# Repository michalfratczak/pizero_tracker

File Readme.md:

## I2C

You need to use software driver to I2C, and therefore, disable bluetooth. This is for rPI 3 and up.

[https://raspberrypi.stackexchange.com/questions/45570/how-do-i-make-serial-work-on-the-raspberry-pi3-or-later-model]

```
sudo rpi-update

nano /boot/config.txt

dtoverlay=pi3-disable-bt
enable_uart=1
dtoverlay=w1-gpio
dtparam=i2c_arm=off
dtparam=i2c=off
#dtoverlay=i2c-gpio,bus=1,i2c_gpio_sda=2,i2c_gpio_scl=3
dtoverlay=i2c-gpio,i2c_gpio_sda=2,i2c_gpio_scl=3
```

## Dependencies

SSDV:

git submodule update --init --recursive

---
sudo apt-get install libboost-program-options-dev

---
git clone https://github.com/zeromq/libzmq.git

build with cmake

---
git clone https://github.com/zeromq/cppzmq.git

build with cmake

---
http://abyz.me.uk/rpi/pigpio/download.html
```
wget https://github.com/joan2937/pigpio/archive/master.zip
unzip master.zip
cd pigpio-master
make
sudo make install
```

---
pip3 install zmq exifread picamera psutil

sudo apt-get install imagemagick

## Run on one thread:

```
taskset -c 1 ./tracker
```

## MTX2 datasheet
http://www.radiometrix.com/files/additional/mtx2.pdf

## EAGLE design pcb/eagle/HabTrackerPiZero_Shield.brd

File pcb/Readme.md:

IMPORTANT:
Powering to 3.3V from a regulator does not work here.
Instead, use 5V regulator and connect to 5V pin.

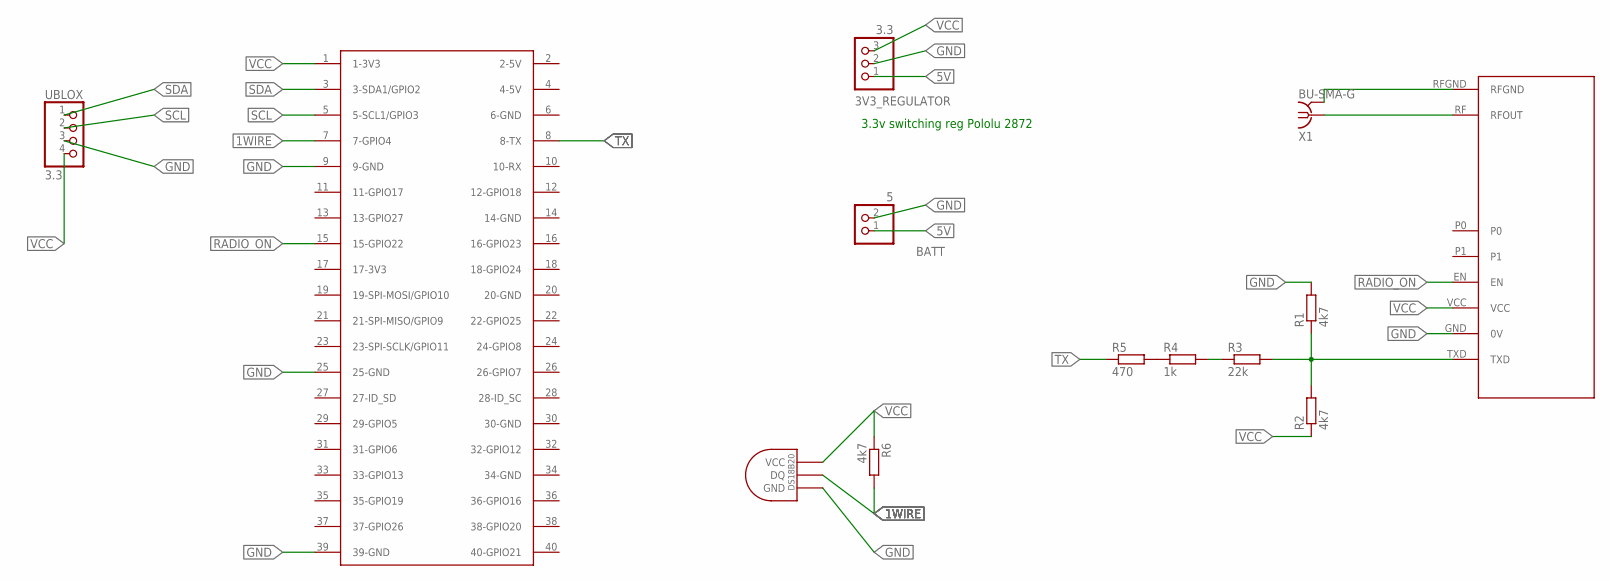
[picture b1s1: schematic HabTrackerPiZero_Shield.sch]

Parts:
3V3_REGULATOR: 3.3; 1X03
BATT: 5; 1X02
R1, R2, R6: 4k7; 0204/7
R3: 22k; 0204/7
R4: 1k; 0204/7
R5: 470; 0204/7
U$1: RASPBERRY-PI+PIZERO; RASPBERRY-PI-ZERO
U$2: DS1820TO92; DS1820
U$3: RADIOMETRIX-MTX2
UBLOX: 3.3; 1X04
X1: BU-SMA-G

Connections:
1WIRE: R6.2, U$1.7 (7-GPIO4), U$2.DQ
5V: 3V3_REGULATOR.1, BATT.1
GND: 3V3_REGULATOR.2, BATT.2, R1.2, U$1.9 (9-GND), U$1.25 (25-GND), U$1.39 (39-GND), U$2.GND, U$3.GND (0V), UBLOX.3
unnamed: R1.1, R2.2, R3.2, U$3.TXD
unnamed: U$3.RF (RFOUT), X1.1
unnamed: U$3.RFGND, X1.2, X1.3 (2), X1.4 (2), X1.5 (2)
unnamed: R4.1, R5.2
unnamed: R3.1, R4.2
RADIO_ON: U$1.15 (15-GPIO22), U$3.EN
SCL: U$1.5 (5-SCL1/GPIO3), UBLOX.2
SDA: U$1.3 (3-SDA1/GPIO2), UBLOX.1
TX: R5.1, U$1.8 (8-TX)
VCC: 3V3_REGULATOR.3, R2.1, R6.1, U$1.1 (1-3V3), U$2.VDD (VCC), U$3.VCC, UBLOX.4

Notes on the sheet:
3.3v switching reg Pololu 2872

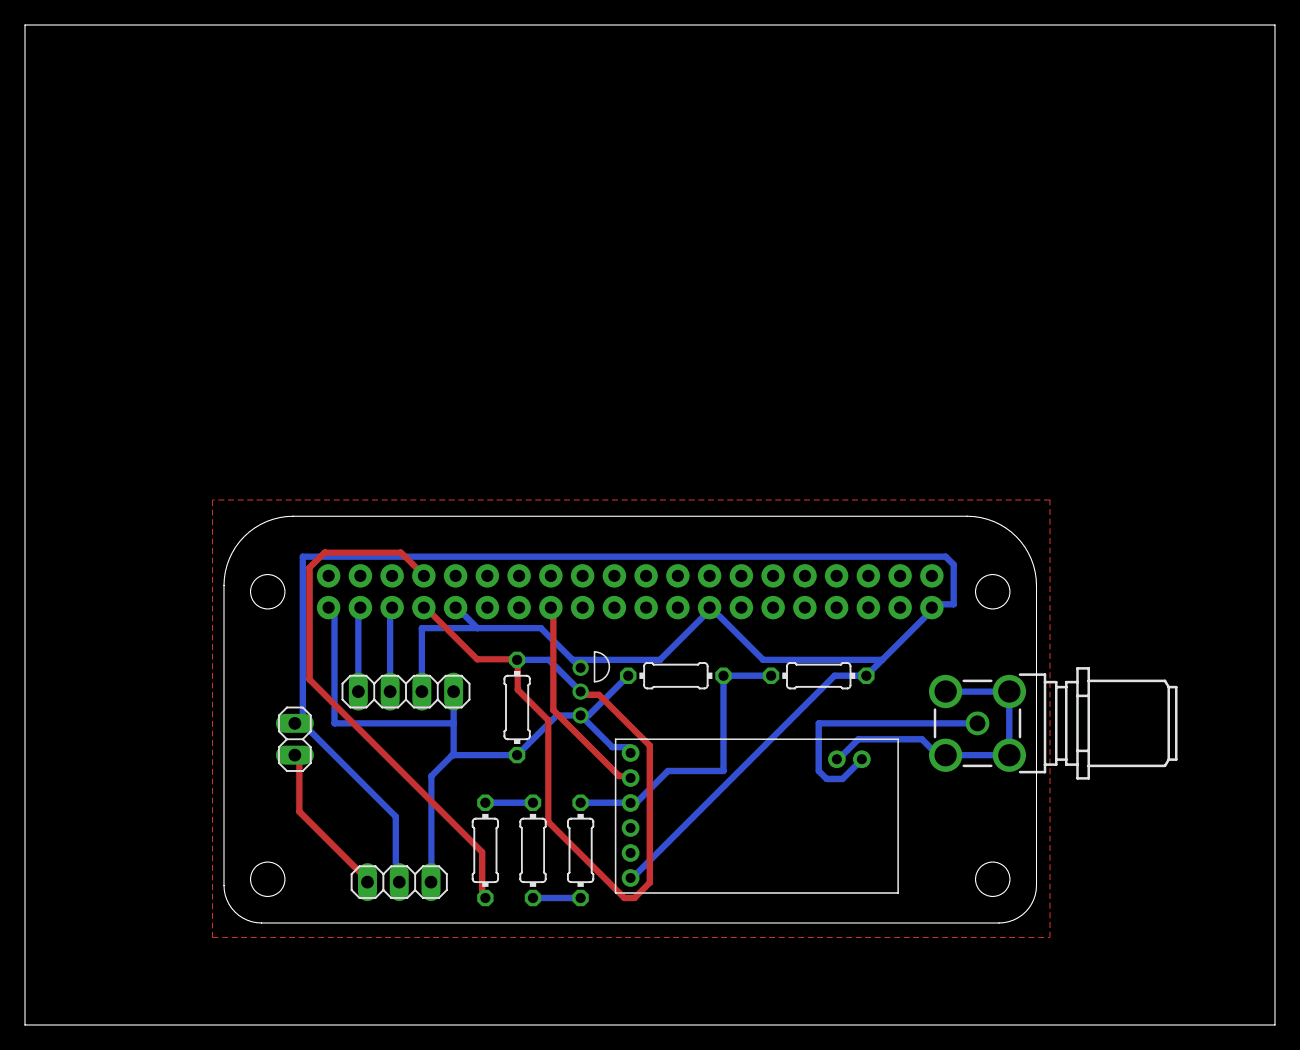
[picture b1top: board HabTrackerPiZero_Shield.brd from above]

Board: 2 copper layers, 100.0 x 80.0 mm, 13 parts (0 on the bottom side), 13 nets.

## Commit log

2020-03-29 add nmea and uBlox code
2020-03-29 uBlox move some code between files
2020-03-30 mtx2b init
2020-03-31 mtx2b - baud_t type
2020-03-31 eagle PCB files for board shield
2020-04-01 mtx2 wip
2020-04-01 squash mtx2 devel branch
2020-04-01 squash ds18b20 devel branch
2020-04-01 Readme.md
2020-04-01 dsb18b20 crc regexp fix
2020-04-01 minimal main tracker code
2020-04-02 tracker main.cpp minor cleanup
2020-04-02 improved NMEA scanning
2020-04-02 some nmea comments
2020-04-02 remove deg2decim from NMEA iface
2020-04-02 some formatting
2020-04-05 test message in UKHAS format
2020-04-08 Use NMEA_get_last_msg in ublox test
2020-04-08 main tracker: properly parse NMEA from uBlox
2020-04-08 nmea_t::utc is now char[6]
2020-04-08 fix nmea utc string formatting
2020-04-09 Add https://github.com/fsphil/ssdv
2020-04-09 ssdv CMake and test JPEG file
2020-04-09 example SSDV send
2020-04-09 remove k100 baud speed
2020-04-09 uBLOX as thread
2020-04-09 ssdv delete image after send
2020-04-10 Initial ZeroMQ. Private GLOB::nmea
2020-04-10 nmea_t comments. Add temp sensor to GLOB.
2020-04-11 msg_num CLI. baud_t : int.
2020-04-11 sensors thread
2020-04-11 static cppzmq linking
2020-04-11 add service file
2020-04-11 device acquire in loop. NMEA report UTC from incomplete sentences.
2020-04-11 Don't send SSDV when no fix. Added nmea_t::seconds()
2020-04-13 Fix CTRL_C in mainloop
2020-04-13 wip - cleanup
2020-04-13 dynamics
2020-04-14 nmea_t utc_as_seconds
2020-04-14 improved test zmq client
2020-04-15 Better GPS handling. Improved nmea parsing. Beter fix validation.
2020-04-15 Fixed clock in dynamics_t. All sensors in G.dynamics_
2020-04-15 basic camera.py
2020-04-15 camera.py zmq client
2020-04-15 JSON structure change.
2020-04-16 readme
2020-04-16 Fix bug in RMC parsing.
2020-04-16 Fixed dynamics_t
2020-04-16 dyncamics_t fixed dT
2020-04-16 dynamics_t: value always up-to-date
2020-04-16 code comments
2020-04-16 Fixed nmea reuse inmain loop
2020-04-16 dynamics_t improvements. with averaging.
2020-04-16 camera.py wip
2020-04-16 camera wip
2020-04-17 Camera WIP. camera.service. Always send SSDV.
2020-04-23 ssdv rename tile to packet
2020-05-12 setproctitle camera.py
2020-05-13 ssdv: delete file if failed to load data.
2020-05-13 tracker: fix json formatting
2020-05-13 camera minor WIP
2020-05-13 resume msg_id
2020-06-01 some comments on gps parsing
2020-06-02 set WorkingDirectory in tracker.service
2020-06-02 nmea: fix speed unit. convert knots to m/s
2020-06-03 Added pololu part number do schematics
2020-06-04 Send runtime seconds with telemetry.
2020-06-15 Add 10 to last msg_id read from file.
2020-06-15 Add watchdog
2020-06-22 move camera.py to python3
2020-06-23 Added async_log_t for async file logging
2020-06-25 camera.py watch disk usage
2020-06-25 camera: save SSDV id to disk and restart from that. Also Fix counting of lo_res photo interval.
2020-06-26 Add state server Try predicting one of states: kUnknown, kStandBy, kAscend, kDescend, kFreefall, kLanded. Needs launch location lat lon alt. Stop Camera on kLand. Stop SSDV on kFreefall and kLand. Ad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
2020-06-26 Added loging
2020-06-26 Add WorkingDirectory=/boot to camera.service
2020-06-27 watchdog for multiple threads
2020-06-29 update camera resolution to cam v2
2020-06-29 NMEA_msg_checksum_ok msg size check
2020-07-22 PCB: move reg away from corner hole
2020-07-23 wrong case in include. readme update.
2020-07-23 Add tracker.cfg
2020-07-25 Readme upd
2020-08-13 Track current nmea and last valid nmea. Transmit current, even if not valid.
2020-08-25 Improve nmea_t type and fix altitude not being recorded. Adjust flight state logic.
2020-08-27 camera: disable VIDEO in kLanded state. Send hiRes
2020-08-27 hot bugfix to camera.py
2020-08-27 Stop camera on GPS fix loss.
2020-12-14 Added PCB readme
2023-10-12 PDF of schematic
